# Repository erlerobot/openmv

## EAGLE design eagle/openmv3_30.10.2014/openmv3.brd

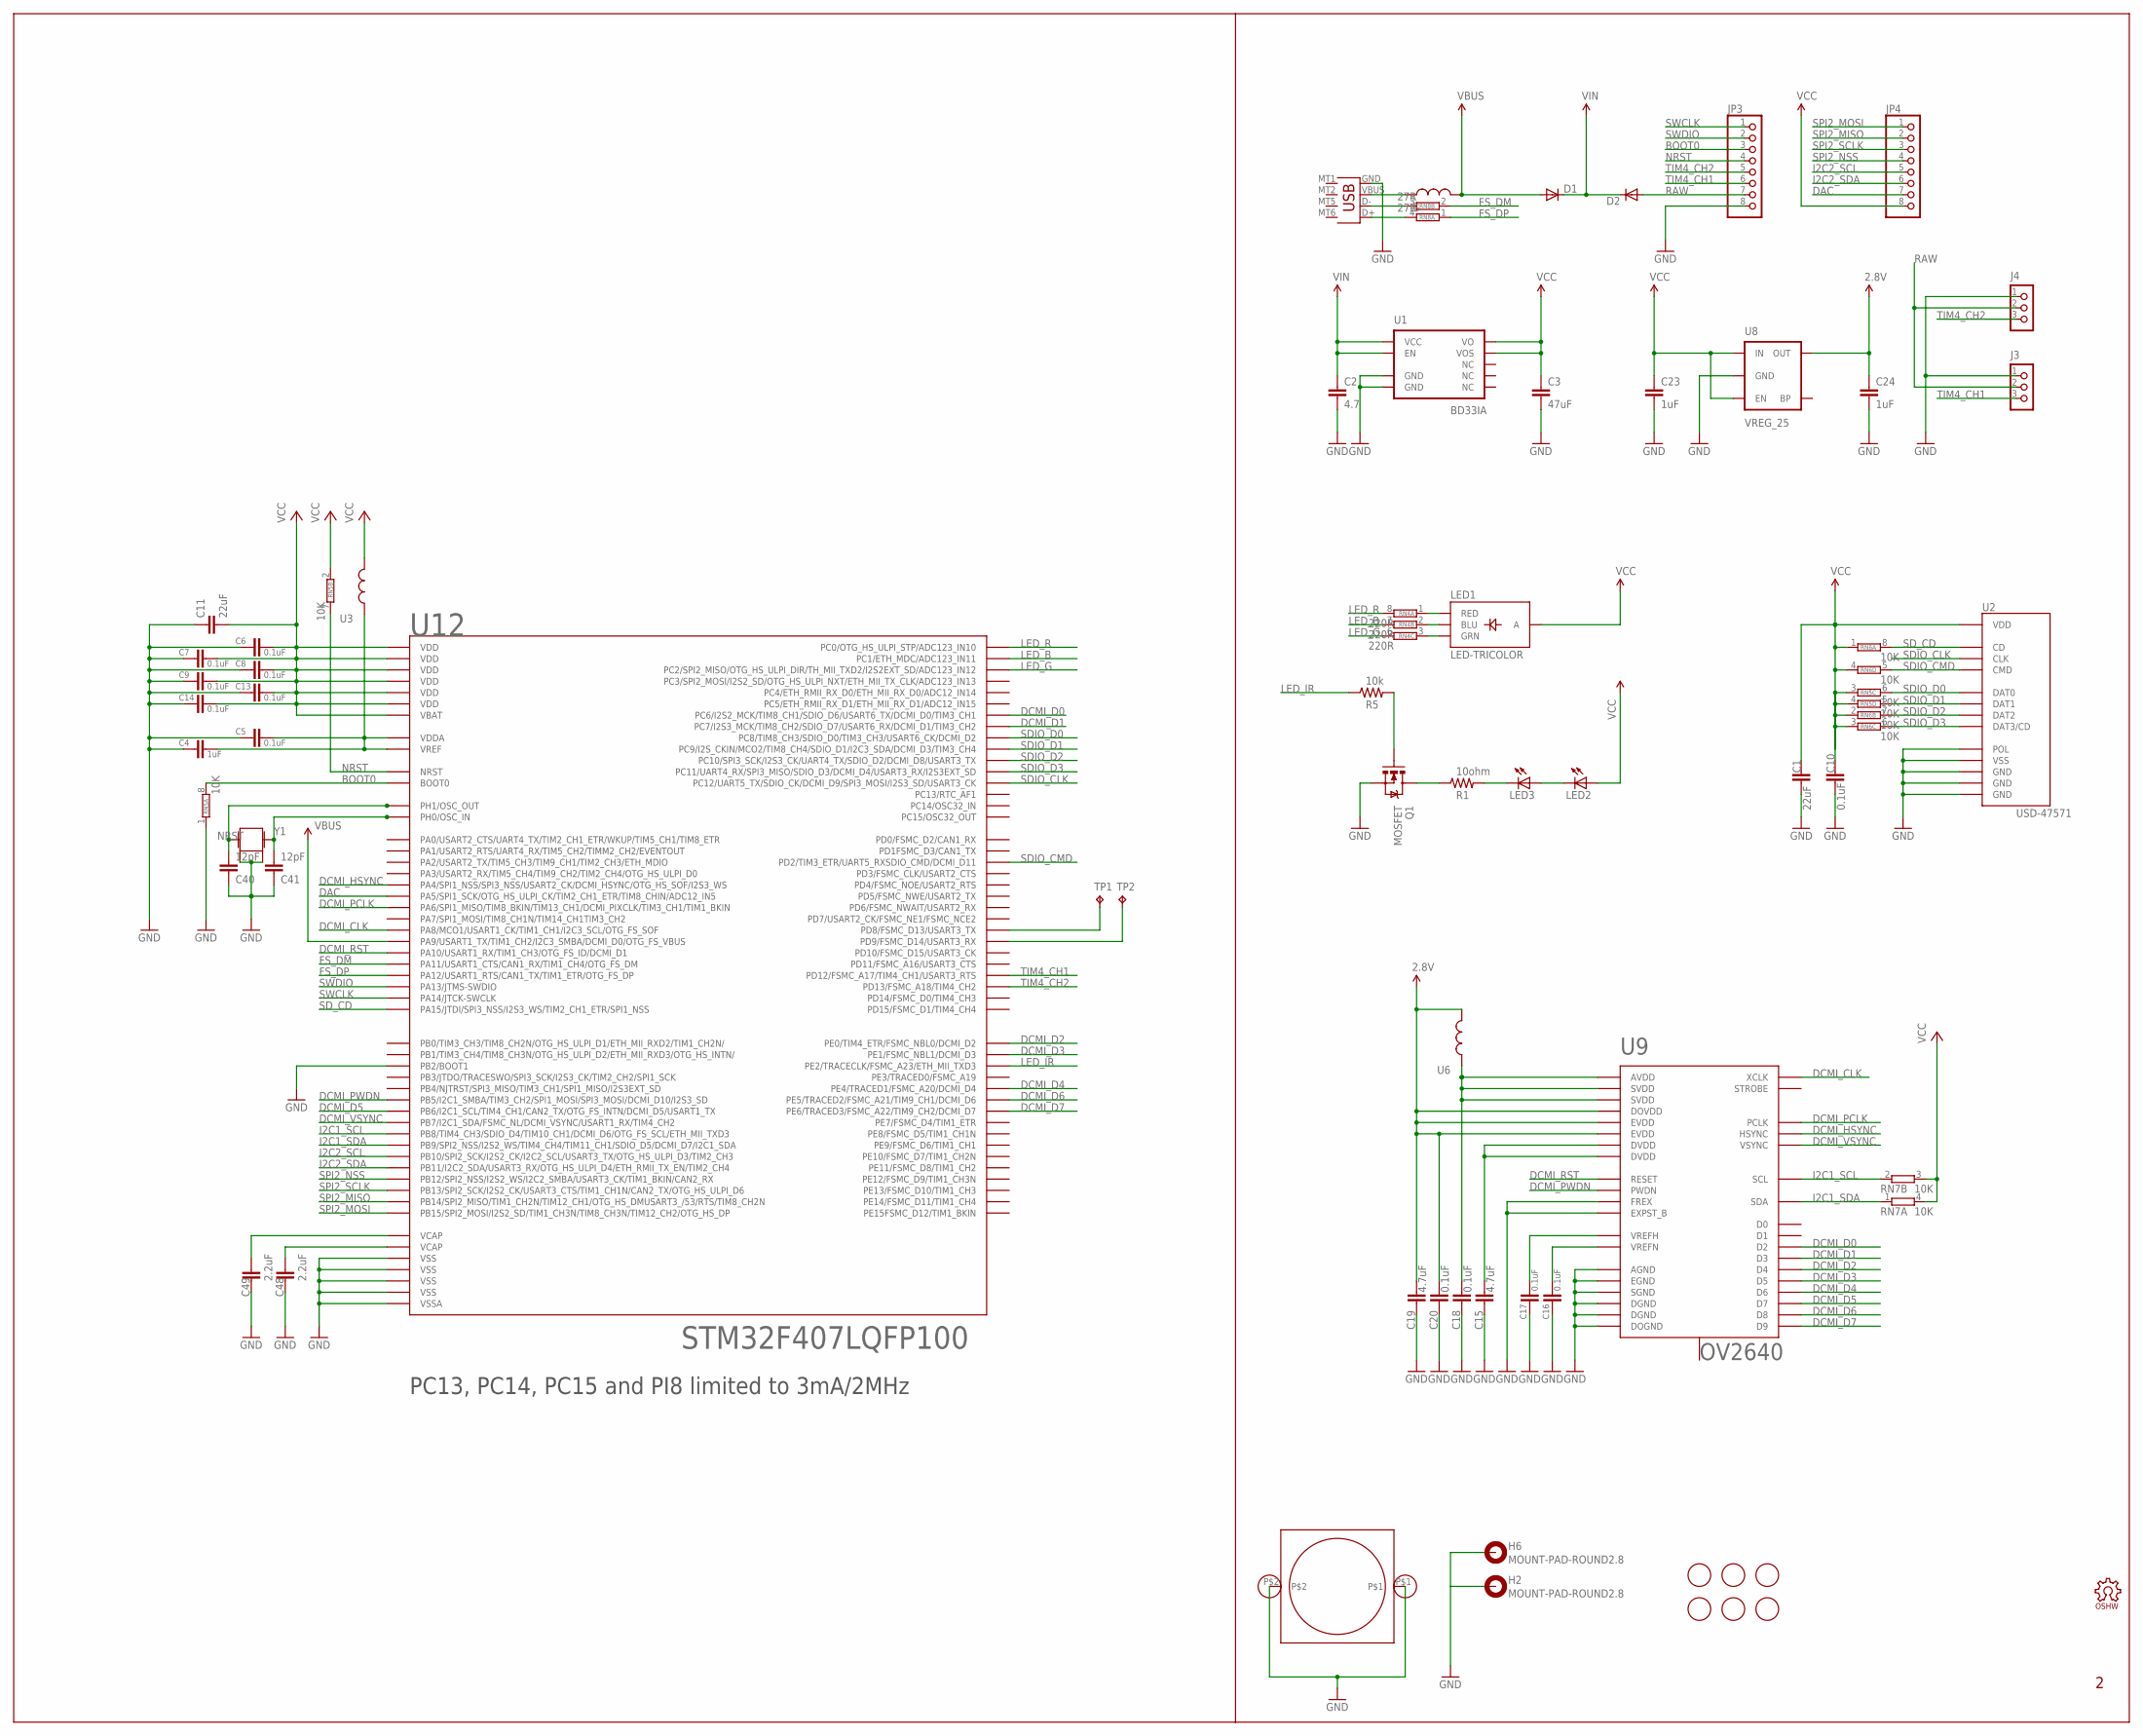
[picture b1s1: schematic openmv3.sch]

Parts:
C1, C11: 22uF; 0805
C2: 4.7; 0603-CAP
C3: 47uF; 1206
C4, C23, C24: 1uF; 0603-CAP
C5, C6, C7, C8, C9, C10, C13, C14, C16, C17, C18, C20: 0.1uF; 0603-CAP
C15, C19: 4.7uF; 0603-CAP
C40, C41: 12pF; 0603-CAP
C48, C49: 2.2uF; 0603-CAP
D1, D2: DIODESOD; SOD-323
H2, H6: MOUNT-PAD-ROUND2.8; 2,8-PAD
J3, J4: CON_HEADER_1X03; M1X3_SMD
JP3, JP4: PINHD-1X8; 1X08
LED1: LED-TRICOLOR; LED-TRICOLOR-SMD
LED2, LED3: LED3MM
LOGO1: OSHW_LOGO_FILLX0150-NT; OSHW_FILLX150_NOTEXT
Q1: MOSFET; SOT23-3
R1: 10ohm; 0603-RES
R5: 10k; 0603-RES
RN4: 220R; EXBV8V
RN5, RN6: 10K; EXBV8V
RN7: 10K; EXBV4V
RN8: 27R; EXBV4V
TP1, TP2: TPTP12R; TP12R
U1: BD33IA; HTSOP-J8
U2: USD-47571
U3, U6, U7: INDUCTOR0603; 0603
U8: VREG_25; SOT23-5
U9: OV2640; CSP2
U12: STM32F407LQFP100; LQFP100
U$1: LENSMOUNT20MM; LENSMOUNT-20MM
U$14, U$15, U$16, U$17, U$19, U$20: FIDUCIAL; FIDUCIAL_1MM
X2: USB-MICROB
Y1: CRYSTAL2.5X2.0; CRYSTAL-2.5X2.0

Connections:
2.8V: C19.1, C20.1, C24.1, U6.2, U8.5 (OUT), U9.B1 (DOVDD), U9.F1 (EVDD), U9.G1 (EVDD)
BOOT0: JP3.3, RN5.8 (2), U12.94 (BOOT0)
DAC: JP4.7, U12.30 (PA5/SPI1_SCK/OTG_HS_ULPI_CK/TIM2_CH1_ET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)
DCMI_CLK: U9.C4 (XCLK), U12.67 (PA8/MCO1/USART1_CK/TIM1_CH1/I2C3_SCL/OT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)
DCMI_D0: U9.F3 (D2), U12.63 (PC6/I2S2_MCK/TIM8_CH1/SDIO_D6/USART6_TX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)
DCMI_D1: U9.G3 (D3), U12.64 (PC7/I2S3_MCK/TIM8_CH2/SDIO_D7/USART6_RX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)
DCMI_D2: U9.F4 (D4), U12.97 (PE0/TIM4_ETR/FSMC_NBL0/DCMI_D2)
DCMI_D3: U9.G4 (D5), U12.98 (PE1/FSMC_NBL1/DCMI_D3)
DCMI_D4: U9.E5 (D6), U12.3 (PE4/TRACED1/FSMC_A20/DCMI_D4)
DCMI_D5: U9.G5 (D7), U12.92 (PB6/I2C1_SCL/TIM4_CH1/CAN2_TX/OTG_FS_IN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)
DCMI_D6: U9.F5 (D8), U12.4 (PE5/TRACED2/FSMC_A21/TIM9_CH1/DCMI_D6)
DCMI_D7: U9.G6 (D9), U12.5 (PE6/TRACED3/FSMC_A22/TIM9_CH2/DCMI_D7)
DCMI_HSYNC: U9.C3 (HSYNC), U12.29 (PA4/SPI1_NSS/SPI3_NSS/USART2_CK/DCMI_HS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)
DCMI_PCLK: U9.E3 (PCLK), U12.31 (PA6/SPI1_MISO/TIM8_BKIN/TIM13_CH1/DCMI_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)
DCMI_PWDN: U9.B6 (PWDN), U12.91 (PB5/I2C1_SMBA/TIM3_CH2/SPI1_MOSI/SPI3_M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)
DCMI_RST: U9.C6 (RESET), U12.69 (PA10/USART1_RX/TIM1_CH3/OTG_FS_ID/DCMI_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)
DCMI_VSYNC: U9.D2 (VSYNC), U12.93 (PB7/I2C1_SDA/FSMC_NL/DCMI_VSYNC/USART1_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)
FS_DM: RN8.2 (1), U12.70 (PA11/USART1_CTS/CAN1_RX/TIM1_CH4/OTG_FS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)
FS_DP: RN8.1, U12.71 (PA12/USART1_RTS/CAN1_TX/TIM1_ETR/OTG_FS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)
GND: C1.2, C2.2, C3.2, C4.2, C5.2, C6.2, C7.2, C8.2, C9.2, C10.2, C11.1, C13.2, C14.2, C15.2, C16.2, C17.2, C18.2, C19.2, C20.2, C23.2, C24.2, C40.1, C41.1, C48.2, C49.2, H2.B2,8, H6.B2,8, J3.1, J4.1, JP3.8, Q1.2 (S), RN5.1, U1.3 (GND), U1.P$1 (GND), U2.G$1 (GND), U2.G$2 (GND), U2.G$3 (GND), U2.G$4 (POL), U2.P$6 (VSS), U8.2 (GND), U9.A1 (DOGND), U9.A2 (EXPST_B), U9.A3 (AGND), U9.A4 (SGND), U9.B2 (FREX), U9.E4 (EGND), U9.E6 (DGND), U9.G2 (DGND), U12.10 (VSS), U12.20 (VSSA), U12.27 (VSS), U12.37 (PB2/BOOT1), U12.74 (VSS), U12.99 (VSS), U$1.P$1, U$1.P$2, X2.GND, Y1.2, Y1.4
I2C1_SCL: RN7.2 (1), U9.C2 (SCL), U12.95 (PB8/TIM4_CH3/SDIO_D4/TIM10_CH1/DCMI_D6/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)
I2C1_SDA: RN7.1, U9.C1 (SDA), U12.96 (PB9/SPI2_NSS/I2S2_WS/TIM4_CH4/TIM11_CH1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)
I2C2_SCL: JP4.5, U12.47 (PB10/SPI2_SCK/I2S2_CK/I2C2_SCL/USART3_T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)
I2C2_SDA: JP4.6, U12.48 (PB11/I2C2_SDA/USART3_RX/OTG_HS_ULPI_D4/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)
LED_B: RN4.7 (2), U12.16 (PC1/ETH_MDC/ADC123_IN11)
LED_G: RN4.6 (2), U12.17 (PC2/SPI2_MISO/OTG_HS_ULPI_DIR/TH_MII_TX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)
LED_IR: R5.1, U12.1 (PE2/TRACECLK/FSMC_A23/ETH_MII_TXD3)
LED_R: RN4.8 (2), U12.15 (PC0/OTG_HS_ULPI_STP/ADC123_IN10)
unnamed: C17.1, U9.C5 (VREFH)
unnamed: C40.2, U12.13 (PH1/OSC_OUT), Y1.3 (2)
unnamed: C16.1, U9.A5 (VREFN)
unnamed: C41.2, U12.12 (PH0/OSC_IN), Y1.1
unnamed: Q1.1 (G), R5.2
unnamed: C15.1, U9.F2 (DVDD), U9.F6 (DVDD)
unnamed: U7.1, X2.VBUS
unnamed: LED1.R (RED), RN4.1
unnamed: LED1.G (GRN), RN4.3 (1)
unnamed: LED3.K (C), R1.2
unnamed: LED1.B (BLU), RN4.2 (1)
unnamed: C4.1, C5.1, U3.1, U12.21 (VREF), U12.22 (VDDA)
unnamed: C18.1, U6.1, U9.B3 (AVDD), U9.B4 (SVDD), U9.B5 (SVDD)
unnamed: Q1.3 (D), R1.1
unnamed: RN8.3 (2), X2.D-
unnamed: LED2.K (C), LED3.A
unnamed: RN8.4 (2), X2.D+
unnamed: TP1.TP, U12.55 (PD8/FSMC_D13/USART3_TX)
unnamed: TP2.TP, U12.56 (PD9/FSMC_D14/USART3_RX)
NRST: JP3.4, RN5.7 (2), U12.14 (NRST)
RAW: D2.2 (A), J3.2, J4.2, JP3.7
SDIO_CLK: U2.P$5 (CLK), U12.80 (PC12/UART5_TX/SDIO_CK/DCMI_D9/SPI3_MOSI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)
SDIO_CMD: RN6.5 (2), U2.P$3 (CMD), U12.83 (PD2/TIM3_ETR/UART5_RXSDIO_CMD/DCMI_D11)
SDIO_D0: RN5.6 (2), U2.P$7 (DAT0), U12.65 (PC8/TIM8_CH3/SDIO_D0/TIM3_CH3/USART6_CK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)
SDIO_D1: RN5.5 (2), U2.P$8 (DAT1), U12.66 (PC9/I2S_CKIN/MCO2/TIM8_CH4/SDIO_D1/I2C3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)
SDIO_D2: RN6.7 (2), U2.P$1 (DAT2), U12.78 (PC10/SPI3_SCK/I2S3_CK/UART4_TX/SDIO_D2/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)
SDIO_D3: RN6.6 (2), U2.P$2 (DAT3/CD), U12.79 (PC11/UART4_RX/SPI3_MISO/SDIO_D3/DCMI_D4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)
SD_CD: RN6.8 (2), U2.G$5 (CD), U12.77 (PA15/JTDI/SPI3_NSS/I2S3_WS/TIM2_CH1_ETR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)
SPI2_MISO: JP4.2, U12.53 (PB14/SPI2_MISO/TIM1_CH2N/TIM12_CH1/OTG_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)
SPI2_MOSI: JP4.1, U12.54 (PB15/SPI2_MOSI/I2S2_SD/TIM1_CH3N/TIM8_C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)
SPI2_NSS: JP4.4, U12.51 (PB12/SPI2_NSS/I2S2_WS/I2C2_SMBA/USART3_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)
SPI2_SCLK: JP4.3, U12.52 (PB13/SPI2_SCK/I2S2_CK/USART3_CTS/TIM1_C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)
SWCLK: JP3.1, U12.76 (PA14/JTCK-SWCLK)
SWDIO: JP3.2, U12.72 (PA13/JTMS-SWDIO)
TIM4_CH1: J3.3, JP3.6, U12.59 (PD12/FSMC_A17/TIM4_CH1/USART3_RTS)
TIM4_CH2: J4.3, JP3.5, U12.60 (PD13/FSMC_A18/TIM4_CH2)
VBUS: D1.2 (A), U7.2, U12.68 (PA9/USART1_TX/TIM1_CH2/I2C3_SMBA/DCMI_D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)
VCAP1: C49.1, U12.49 (VCAP)
VCAP2: C48.1, U12.73 (VCAP)
VCC: C1.1, C3.1, C6.1, C7.1, C8.1, C9.1, C10.1, C11.2, C13.1, C14.1, C23.1, JP4.8, LED1.A, LED2.A, RN5.2 (1), RN5.3 (1), RN5.4 (1), RN6.1, RN6.2 (1), RN6.3 (1), RN6.4 (1), RN7.3 (2), RN7.4 (2), U1.1 (VO), U1.2 (VOS), U2.P$4 (VDD), U3.2, U8.1 (IN), U8.3 (EN), U12.6 (VBAT), U12.11 (VDD), U12.19 (VDD), U12.28 (VDD), U12.50 (VDD), U12.75 (VDD), U12.100 (VDD)
VIN: C2.1, D1.1 (C), D2.1 (C), U1.5 (EN), U1.8 (VCC)

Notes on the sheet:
PC13, PC14, PC15 and PI8 limited to 3mA/2MHz

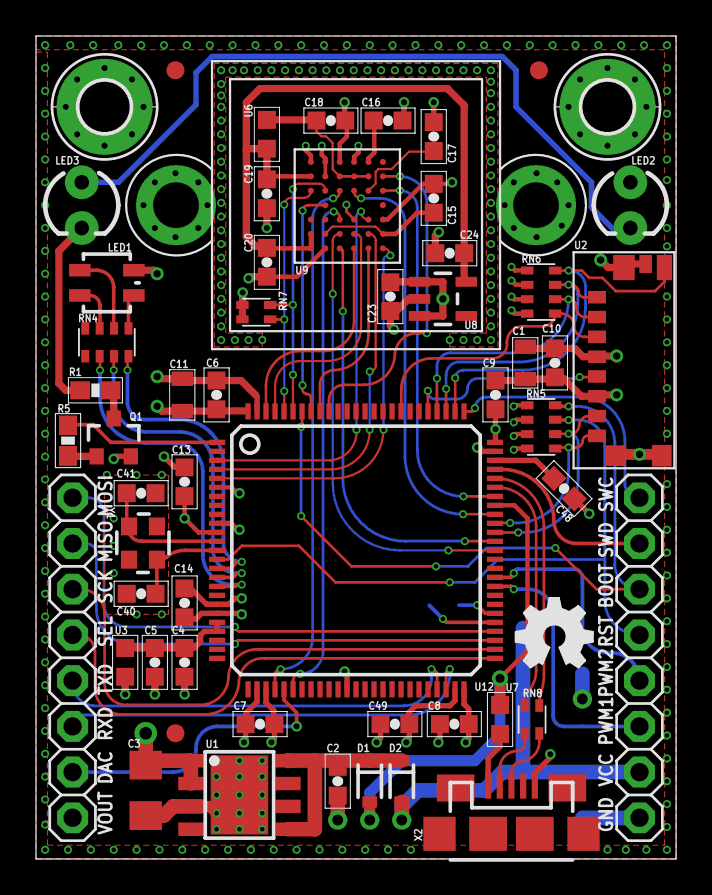
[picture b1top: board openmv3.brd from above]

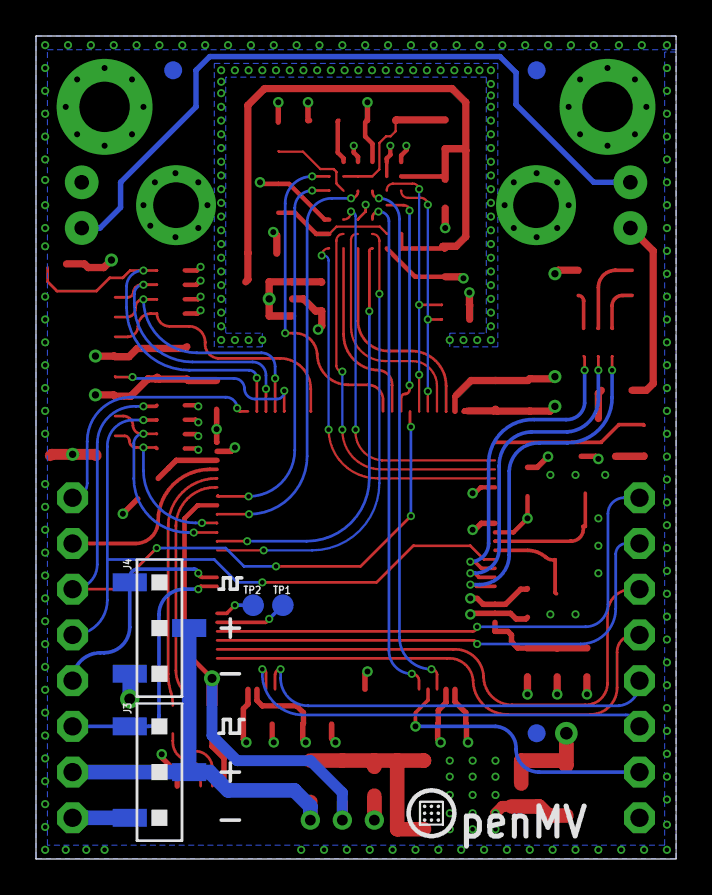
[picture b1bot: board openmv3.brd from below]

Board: 4 copper layers, 35.6 x 45.7 mm, 64 parts (7 on the bottom side), 69 nets.

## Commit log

2014-10-28 Add manufacturing files
2014-10-28 BOM fill out: capacitors
2014-10-30 Add Openmv3 files
2014-10-30 openmv3 BOM first version
2014-10-31 Add latest version folder, create the BOM
2014-11-04 Add files ready to manufacture, stackup left
2014-11-04 Add pcb stackup file
2014-11-05 Add stackup

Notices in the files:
eagle/openmv3/openmv3.sch:
Copyright (c) 2013 Ibrahim Abd Elkader
This work is licensed under the Creative Commons Attribution-ShareAlike 3.0 License.
To view a copy of this license, visit http://creativecommons.org/licenses/by-sa/3.0
